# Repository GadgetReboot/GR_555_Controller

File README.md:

# GR_555_Controller
Controlling 555's using digital pots over I2C

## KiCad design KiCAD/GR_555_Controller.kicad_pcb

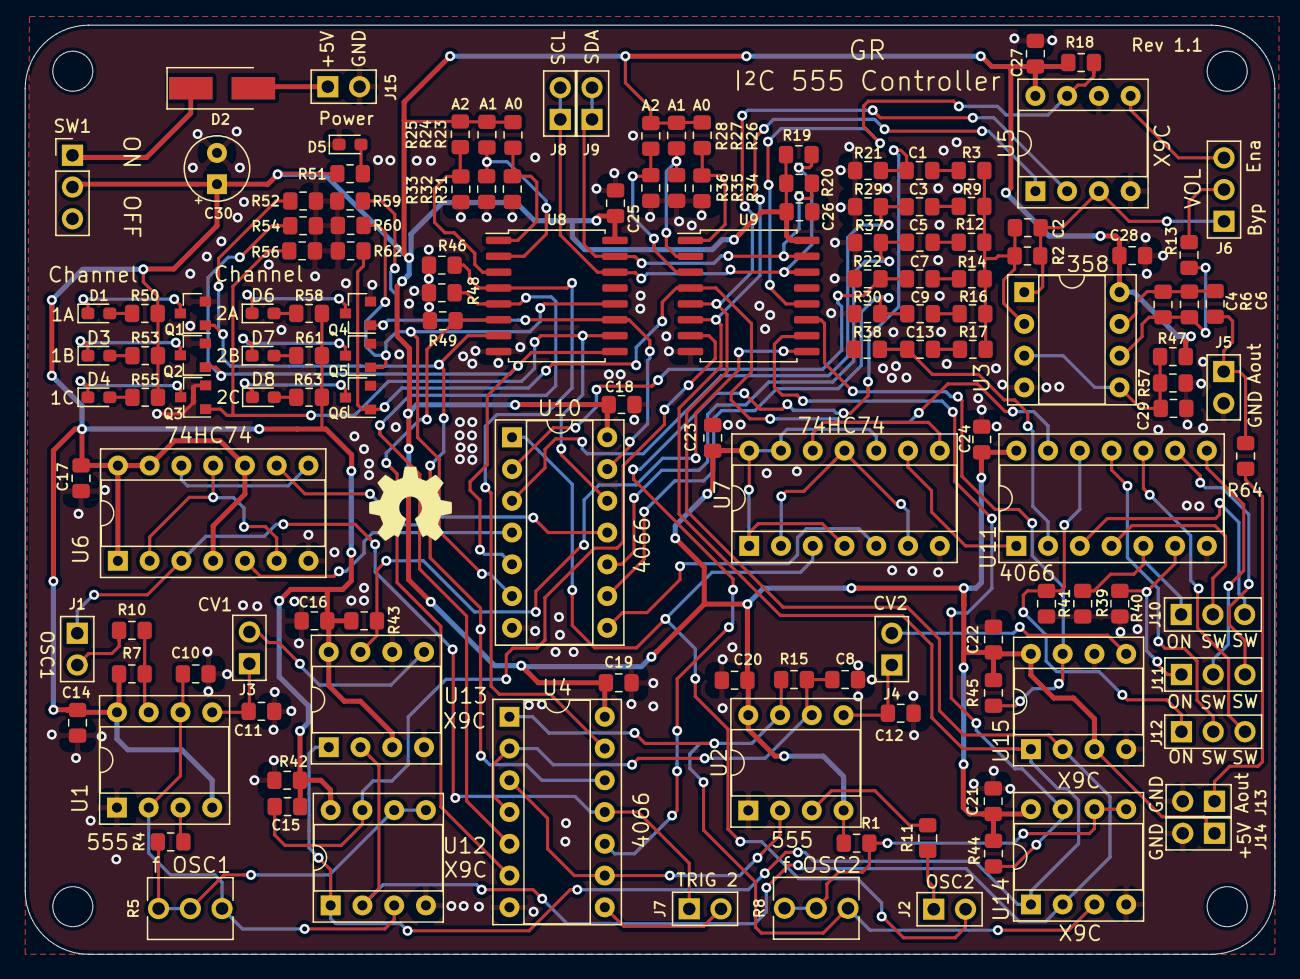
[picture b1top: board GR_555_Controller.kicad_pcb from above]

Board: 2 copper layers, 99.9 x 74.3 mm, 139 parts (0 on the bottom side), 97 nets.

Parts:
C1, C3, C5, C7, C9, C13: 1uF; C_0805_2012Metric_Pad1.15x1.40mm_HandSolder
C2, C4: DNI; C_0805_2012Metric_Pad1.15x1.40mm_HandSolder
C6: 10uF; C_0805_2012Metric_Pad1.15x1.40mm_HandSolder
C8, C10: 47nF; C_0805_2012Metric_Pad1.15x1.40mm_HandSolder
C11, C12: 10nF; C_0805_2012Metric_Pad1.15x1.40mm_HandSolder
C14, C15, C16, C17, C18, C19, C20, C21, C22, C23, C24, C25, C26, C27, C28, C29: 100nF; C_0805_2012Metric_Pad1.15x1.40mm_HandSolder
C30: 10uF; CP_Radial_Tantal_D5.0mm_P2.50mm
D1, D3, D4, D6, D7, D8: LED; LED_0603_1608Metric_Pad1.05x0.95mm_HandSolder
D2: D_Schottky_Small_ALT; D_SMA_Handsoldering
D5: Power; LED_0603_1608Metric_Pad1.05x0.95mm_HandSolder
J1, J2, J3, J4, J5, J7, J8, J9, J13, J14, J15: 1x2; PinHeader_1x02_P2.54mm_Vertical_H1.0mm
J6, J10, J11, J12: Conn_01x03; PinHeader_1x03_P2.54mm_Vertical_H1.0mm
Q1, Q2, Q3, Q4, Q5, Q6: BSS138; SOT-23
R1, R4, R15: 2K; R_0805_2012Metric_Pad1.15x1.40mm_HandSolder
R2, R50, R51, R53, R55, R58, R61, R63: 1K; R_0805_2012Metric_Pad1.15x1.40mm_HandSolder
R3, R14: 6.8K; R_0805_2012Metric_Pad1.15x1.40mm_HandSolder
R5, R8: 100K; Potentiometer_Green
R6, R7, R9, R11, R12, R13, R16, R17, R19, R20, R28, R31, R32, R33, R34, R35, R39, R40, R41, R47, R57: 10K; R_0805_2012Metric_Pad1.15x1.40mm_HandSolder
R10, R64: 0r; R_0805_2012Metric_Pad1.15x1.40mm_HandSolder
R18, R42, R43, R44, R45: 100K; R_0805_2012Metric_Pad1.15x1.40mm_HandSolder
R21, R22, R23, R24, R25, R26, R27, R29, R30, R36, R37, R38, R46, R48, R49, R52, R54, R56, R59, R60, R62: DNI; R_0805_2012Metric_Pad1.15x1.40mm_HandSolder
SW1: SW_SPDT; PinHeader_1x03_P2.54mm_Vertical
U1, U2: 555; DIP-8_W7.62mm_Socket
U3: TL072; DIP-8_W7.62mm_Socket
U4, U10, U11: 4066; DIP-14_W7.62mm_Socket
U5, U12, U13, U14, U15: X9C; DIP-8_W7.62mm_Socket
U6, U7: 74HC74; DIP-14_W7.62mm_Socket
U8, U9: PCF8574; SOIC-16W_7.5x10.3mm_P1.27mm

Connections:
+5V: C14.1, C15.1, C16.1, C17.1, C18.1, C19.1, C20.1, C21.1, C22.1, C23.1, C24.1, C25.1, C26.1, C27.1, C28.1, C30.1, J14.1, R1.1, R7.1, R18.2, R19.1, R20.1, R23.1, R24.1, R25.1, R26.1, R27.1, R28.1, R42.2, R43.2, R44.2, R45.2, R47.1, R50.2, R51.1, R53.2, R55.2, R58.2, R61.2, R63.2, SW1.2, U1.4, U1.8, U2.4, U2.8, U3.8, U4.14, U5.8, U6.1, U6.4, U6.10, U6.13, U6.14, U7.1, U7.4, U7.10, U7.13, U7.14, U8.16, U9.16, U10.14, U11.14, U12.8, U13.3, U13.8, U14.8, U15.3, U15.8
/555Out1a: J1.1, J7.1, U4.11, U6.3
/555Out1b: U6.5, U10.4
/555Out1c: U6.9, U10.11
/555Out2a: J2.2, U7.3, U10.1
/555Out2b: U7.5, U10.8
/555Out2c: U7.9, U11.1
/A0_CTL1: R23.2, R31.1, U8.1
/A0_CTL2: R26.2, R34.1, U9.1
/A1_CTL1: R24.2, R32.1, U8.2
/A1_CTL2: R27.2, R35.1, U9.2
/A2_CTL1: R25.2, R33.1, U8.3
/A2_CTL2: R28.2, R36.1, U9.3
/A_Out: C6.1, J5.1, R64.2
/CFG1: R46.2, U4.13, U8.4
/CFG2: R48.2, U4.5, U8.5
/CFG3: R49.2, U4.6, U8.6
/CTRL1a: Q1.1, R52.2, U4.12, U8.7
/CTRL1b: Q2.1, R54.2, U8.9, U10.5
/CTRL1c: Q3.1, R56.2, U8.10, U10.12
/CTRL2a: Q4.1, R59.2, U8.11, U10.13
/CTRL2b: Q5.1, R60.2, U8.12, U10.6
/CTRL2c: Q6.1, R62.2, U9.4, U11.13
/Out1a: C1.2, R21.1, U4.10
/Out1b: C3.2, R29.1, U10.3
/Out1c: C5.2, R37.1, U10.10
/Out2a: C7.2, R22.1, U10.2
/Out2b: C9.2, R30.1, U10.9
/Out2c: C13.2, R38.1, U11.2
/RH1: C10.1, R5.3, U1.2, U1.6, U12.3
/RH3: R8.3, R15.1, U2.7, U4.1, U14.3
/RW1: R4.2, R5.1, R5.2, U12.5, U12.6
/RW2: J3.2, U13.5
/RW3: R1.2, R8.1, R8.2, U14.5, U14.6
/RW4: J4.2, U15.5
/SCL: J8.1, J8.2, R19.2, U8.14, U9.14
/SDA: J9.1, J9.2, R20.2, U8.15, U9.15
/UpDn: U5.2, U9.5, U12.2, U13.2, U14.2, U15.2
/Vref: C29.1, R47.2, R57.1, U3.3, U3.5
/nCS1: R42.1, U9.7, U12.7
/nCS2: R43.1, U9.9, U13.7
/nCS3: R44.1, U9.10, U14.7
/nCS4: R45.1, U9.11, U15.7
/nCS5: R18.1, U5.7, U9.12
/nINC: U5.1, U9.6, U12.1, U13.1, U14.1, U15.1
GND: C8.2, C10.2, C11.2, C12.2, C14.2, C15.2, C16.2, C17.2, C18.2, C19.2, C20.2, C21.2, C22.2, C23.2, C24.2, C25.2, C26.2, C27.2, C28.2, C29.2, C30.2, D5.1, J5.2, J13.2, J14.2, J15.2, Q1.2, Q2.2, Q3.2, Q4.2, Q5.2, Q6.2, R21.2, R22.2, R29.2, R30.2, R31.2, R32.2, R33.2, R34.2, R35.2, R36.2, R37.2, R38.2, R39.2, R40.2, R41.2, R46.1, R48.1, R49.1, R52.1, R54.1, R56.1, R57.2, R59.1, R60.1, R62.1, U1.1, U2.1, U3.4, U4.7, U5.4, U5.6, U6.7, U7.7, U8.8, U9.8, U10.7, U11.7, U12.4, U13.4, U13.6, U14.4, U15.4, U15.6
unnamed: C1.1, R3.2
unnamed: C2.1, J6.1, R2.1, U3.1, U5.3
unnamed: C2.2, R2.2, R3.1, R9.1, R12.1, R14.1, R16.1, R17.1, U3.2
unnamed: C3.1, R9.2
unnamed: C4.1, C6.2, R6.1, U3.7
unnamed: C4.2, R6.2, R13.1, U3.6
unnamed: C5.1, R12.2
unnamed: C7.1, R14.2
unnamed: C8.1, R15.2, U2.6, U4.2, U4.4
unnamed: C9.1, R16.2
unnamed: C11.1, J3.1, U1.5
unnamed: C12.1, J4.1, U2.5
unnamed: C13.1, R17.2
unnamed: D1.1, Q1.3
unnamed: D1.2, R50.1
unnamed: D2.1, SW1.1
unnamed: D2.2, J15.1
unnamed: D3.1, Q2.3
unnamed: D3.2, R53.1
unnamed: D4.1, Q3.3
unnamed: D4.2, R55.1
unnamed: D5.2, R51.2
unnamed: D6.1, Q4.3
unnamed: D6.2, R58.1
unnamed: D7.1, Q5.3
unnamed: D7.2, R61.1
unnamed: D8.1, Q6.3
unnamed: D8.2, R63.1
unnamed: J1.2, R10.1
unnamed: J2.1, R11.1
unnamed: J6.2, R13.2
unnamed: J6.3, U5.5
unnamed: J7.2, U4.8
unnamed: J10.1, R39.1, U11.5
unnamed: J10.2, U11.4
unnamed: J10.3, U11.3
unnamed: J11.1, R40.1, U11.6
unnamed: J11.2, U11.8
unnamed: J11.3, U11.9
unnamed: J12.1, R41.1, U11.12
unnamed: J12.2, U11.11
unnamed: J12.3, U11.10
unnamed: J13.1, R64.1
unnamed: R4.1, U1.3
unnamed: R7.2, R10.2, U1.7
unnamed: R11.2, U2.3
unnamed: U2.2, U4.3, U4.9
unnamed: U6.2, U6.6, U6.11
unnamed: U6.8, U6.12
unnamed: U7.2, U7.6, U7.11
unnamed: U7.8, U7.12

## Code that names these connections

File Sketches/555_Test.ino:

/*******************************************************************************
       This is an example for using the X9Cxxx digital potentiometers
       in a 555 oscillator frequency control situation. By controlling
       the pot and changing the oscillator frequency, tones or sound
       effects can be generated by the 555.

       Using two 555's, a stepped tone generator (Atari punk console) can be configured.

       Note:  For this sketch, the PCB must have U12 and U14 removed (X9C freq. pots)
              and instead, connect physical pots to R5 and R8 

       Hardware project:  https://github.com/GadgetReboot/GR_555_Controller
       Tested on Arduino Uno for I2C control
       Libraries used: PCF8574 https://github.com/RobTillaart/Arduino/tree/master/libraries/PCF8574

       Gadget Reboot

*******************************************************************************/

#include <Wire.h>
#include <PCF8574.h>
#define addr1  0x20    // pcf8574 device 1 I2C address
#define addr2  0x21    // pcf8574 device 2 I2C address

// create pcf8574 controller objects
PCF8574 gpioBank1(addr1);
PCF8574 gpioBank2(addr2);

// pcf8574 GPIO assignment for PCB audio channel and digital pot controls

#define CFG1     0     // 0 = on board resistor between 555 #2 discharge-threshold, 1 = bypass resistor
#define CFG2     1     // 0 = open, 1 = short between 555 #2 threshold-trigger
#define CFG3     2     // 0 = 555 #2 trigger unaffected, 1 = 555 #2 triggered from output of 555 #1
#define CTRL1a   3     // 0 = off, 1 = on  555 #1 main oscillator 
#define CTRL1b   4     // 0 = off, 1 = on  555 #1 sub oscillator 1
#define CTRL1c   5     // 0 = off, 1 = on  555 #1 sub oscillator 2
#define CTRL2a   6     // 0 = off, 1 = on  555 #2 main oscillator 
#define CTRL2b   7     // 0 = off, 1 = on  555 #2 sub oscillator 1

#define CTRL2c   0     // 0 = off, 1 = on  555 #2 sub oscillator 2
#define upDn     1     // 0 = down, 1 = up direction for digital pot increments
#define nINC     2     // advance digital pot wiper in set direction
#define nCS1     3     // chip select digital pot 555 #1 frequency 
#define nCS2     4     // chip select digital pot 555 #1 control voltage
#define nCS3     5     // chip select digital pot 555 #2 frequency
#define nCS4     6     // chip select digital pot 555 #2 control voltage 
#define nCS5     7     // chip select digital pot output level control

void setup() {

  Wire.begin();       // prepare for I2C communication

  // button inputs 
  pinMode(2, INPUT_PULLUP);  // 555 #1 main osc enable
  pinMode(3, INPUT_PULLUP);  // 555 #1 sub osc 1 enable
  pinMode(4, INPUT_PULLUP);  // 555 #1 sub osc 2 enable
  pinMode(5, INPUT_PULLUP);  // 0 = dual 555 stepped tone mode, 1 = single 555 astable mode

  // initialize PCF8574's and disconnect all audio sources from mixer inputs,
  // configure 555 #2 for astable mode, and keep digital pots on standby
  gpioBank1.begin(0x02); // 555 #2 configured as astable osc, all osc outputs disconnected from mixer inputs
  gpioBank2.begin(0xFC); // digital pots on standby,          all osc outputs disconnected from mixer inputs

  // set potentiometer wiper starting positions
  movePotWiperToPos(90, nCS5);    // output level pot
  movePotWiperToPos(50, nCS2);    // 555 #1 cv pot
  movePotWiperToPos(50, nCS4);    // 555 #2 cv pot

}

void loop() {

  // if button is pressed, enter dual 555 stepped tone mode
  if (!digitalRead(5))
  {
    stepped_tone();                  // configure 555's for stepped tone mode
    gpioBank1.write(CTRL1a, LOW);    // disable 555 #1 main osc audio output
    gpioBank1.write(CTRL2a, HIGH);   // enable 555 #2 main osc audio output
    while (!digitalRead(5))          // stay in this mode until gpio goes high
    {}
    gpioBank1.write(CTRL2a, LOW);    // disable 555 #2 main osc audio output
    astable();                       // switch back to astable mode with audio on 555 #1
  }

  // as long as a button is pressed, enable 555 #1 audio output(s)
  if (!digitalRead(2))
    gpioBank1.write(CTRL1a, HIGH);
  else
    gpioBank1.write(CTRL1a, LOW);

  if (!digitalRead(3))
    gpioBank1.write(CTRL1b, HIGH);
  else
    gpioBank1.write(CTRL1b, LOW);

  if (!digitalRead(4))
    gpioBank1.write(CTRL1c, HIGH);
  else
    gpioBank1.write(CTRL1c, LOW);
}

/*---------------------------------------- 555 config functions -------------------------------*/

// configure 555's for stepped tone mode
void stepped_tone()
{

  // configure 555 #2 for monostable mode, triggered by 555 #1 output
  gpioBank1.write(CFG1, HIGH);  // 555 #2 short discharge to threshold
  gpioBank1.write(CFG2, LOW);   // 555 #2 threshold disconnected from trigger
  gpioBank1.write(CFG3, HIGH);  // 555 #1 output to 555 #2 trigger

}

void astable()
{

  // configure 555 #2 for astable mode and disconnect from 555 #1
  gpioBank1.write(CFG1, LOW);
  gpioBank1.write(CFG2, HIGH);
  gpioBank1.write(CFG3, LOW);

}


/*---------------------------------------- digital pot functions -------------------------------*/

// move a selected potentiometer's wiper a number of steps up or down
void movePotWiper(int steps, byte dir, byte nCS)
{
  int i = (steps > 99) ? 99 : steps;       // must move wiper at least 1 step and no more than 99 steps
  if (i < 1) return;

  gpioBank2.write(upDn, dir);              // set increment direction
  gpioBank2.write(nCS, LOW);               // select target pot
  delayMicroseconds(1);                    // delay >=100nS between nCS and nINC
  while (i--) {
    gpioBank2.write(nINC, LOW);            // move wiper by requested # of steps
    delayMicroseconds(1);                  // nINC must hold state >=1uS
    gpioBank2.write(nINC, HIGH);
    delayMicroseconds(1);
  }
  delayMicroseconds(100);                  // delay >=100uS for wiper to change position

  gpioBank2.write(nINC, LOW);
  delayMicroseconds(1);
  gpioBank2.write(nCS, HIGH);              // de-select chip without saving wiper position in nvm
  delayMicroseconds(1);
  gpioBank2.write(nINC, HIGH);
}

// move a pot's wiper to a specific position from 0-99
// first move the pot all the way to one end, then count steps to target position
// there is no way to read the wiper position
void movePotWiperToPos(int pos, byte nCS)
{
  int i = (pos > 99) ? 99 : pos;           // wiper position can be 0 to 99
  if (i < 0) i = 0;

  movePotWiper(99, 0, nCS);                // move wiper to a known position (end of travel at low terminal)
  movePotWiper(pos, 1, nCS);               // move wiper to intended position from 0-99
}

// move a pot's wiper by a specific number of steps in a certain direction
// this is a relative move, useful when an adjustment is required
// without moving the wiper all the way to one end and back
void trimPotWiper(int steps, byte dir, byte nCS)
{
  int i = (steps > 99) ? 99 : steps;       // wiper can move 1 to 99 steps
  if (i < 1) return;

  movePotWiper(steps, dir, nCS);           // move wiper requested number of steps/direction
}
